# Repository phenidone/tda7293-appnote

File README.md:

# Stereo TDA7293

This is a PCB design for a stereo amplifier, using a TDA7293 for each channel.

## Power

The board requires 36+36V DC for 8R loads.  Filtering caps are included, but 
a bridge rectifier is not as this is expected to be used with a switching supply.

## Unmute

The muting circuits are controlled via an opto-isolated input.  Provide 
5-24VDC on the UNMUTE port to enable the amplifiers.  This port allows the
amplifier to be put into a standby/mute mode, e.g. while preamplifiers are
booting and power supplies are stabilising.

## Components

Input capacitors shall be film-type box capacitors, 5mm lead pitch.

C3 and C9 should be non-polarised 22uF electrolytics, as high-voltage as will
fit in the footprint (8mm with 3.5mm lead pitch).

All resistors in the signal chain (R1, R2, R3, R13, R14, R15) should be thin-film
metal precision resistors.

Loop-break resistors (R7, R8, R17, R18) can be chosen differently in accordance
with different grounding needs, e.g. where multiple modules are powered from a
single PSU but receiving signal from a third preamplifier board.  Their
selection depends on your ground topology.

The output zobels (R5/C6, R16/C12) are probably only necessary with a TDA7294,
and may be omitted if there is absolutely no chance of shorting the amplifier
leads, e.g. through use of insulated plugs instead of bare wires into screw
terminals.  R5 and R16 should be 2W-rated.

## TDA7294

The board charges the bootstrap capacitor from the OUTPUT pin rather than
the BOOTLOAD pin, so this board will also work unmodified with a TDA7294.
That limits the absolute-max supply voltage to 100V rather than 120V, but
the appropriate level is lower than that anyway unless you have a very high
impedance load.

## License

This hardware design is (C) 2021 William Brodie-Tyrrell and is licensed under 
the CERN OHL; see cern_ohl_v_1_2.pdf

## TRL

Rev.A is tested and working, but has not been subjected to EMI or other
regulatory testing.

Rev.B has been manufactured but not tested.

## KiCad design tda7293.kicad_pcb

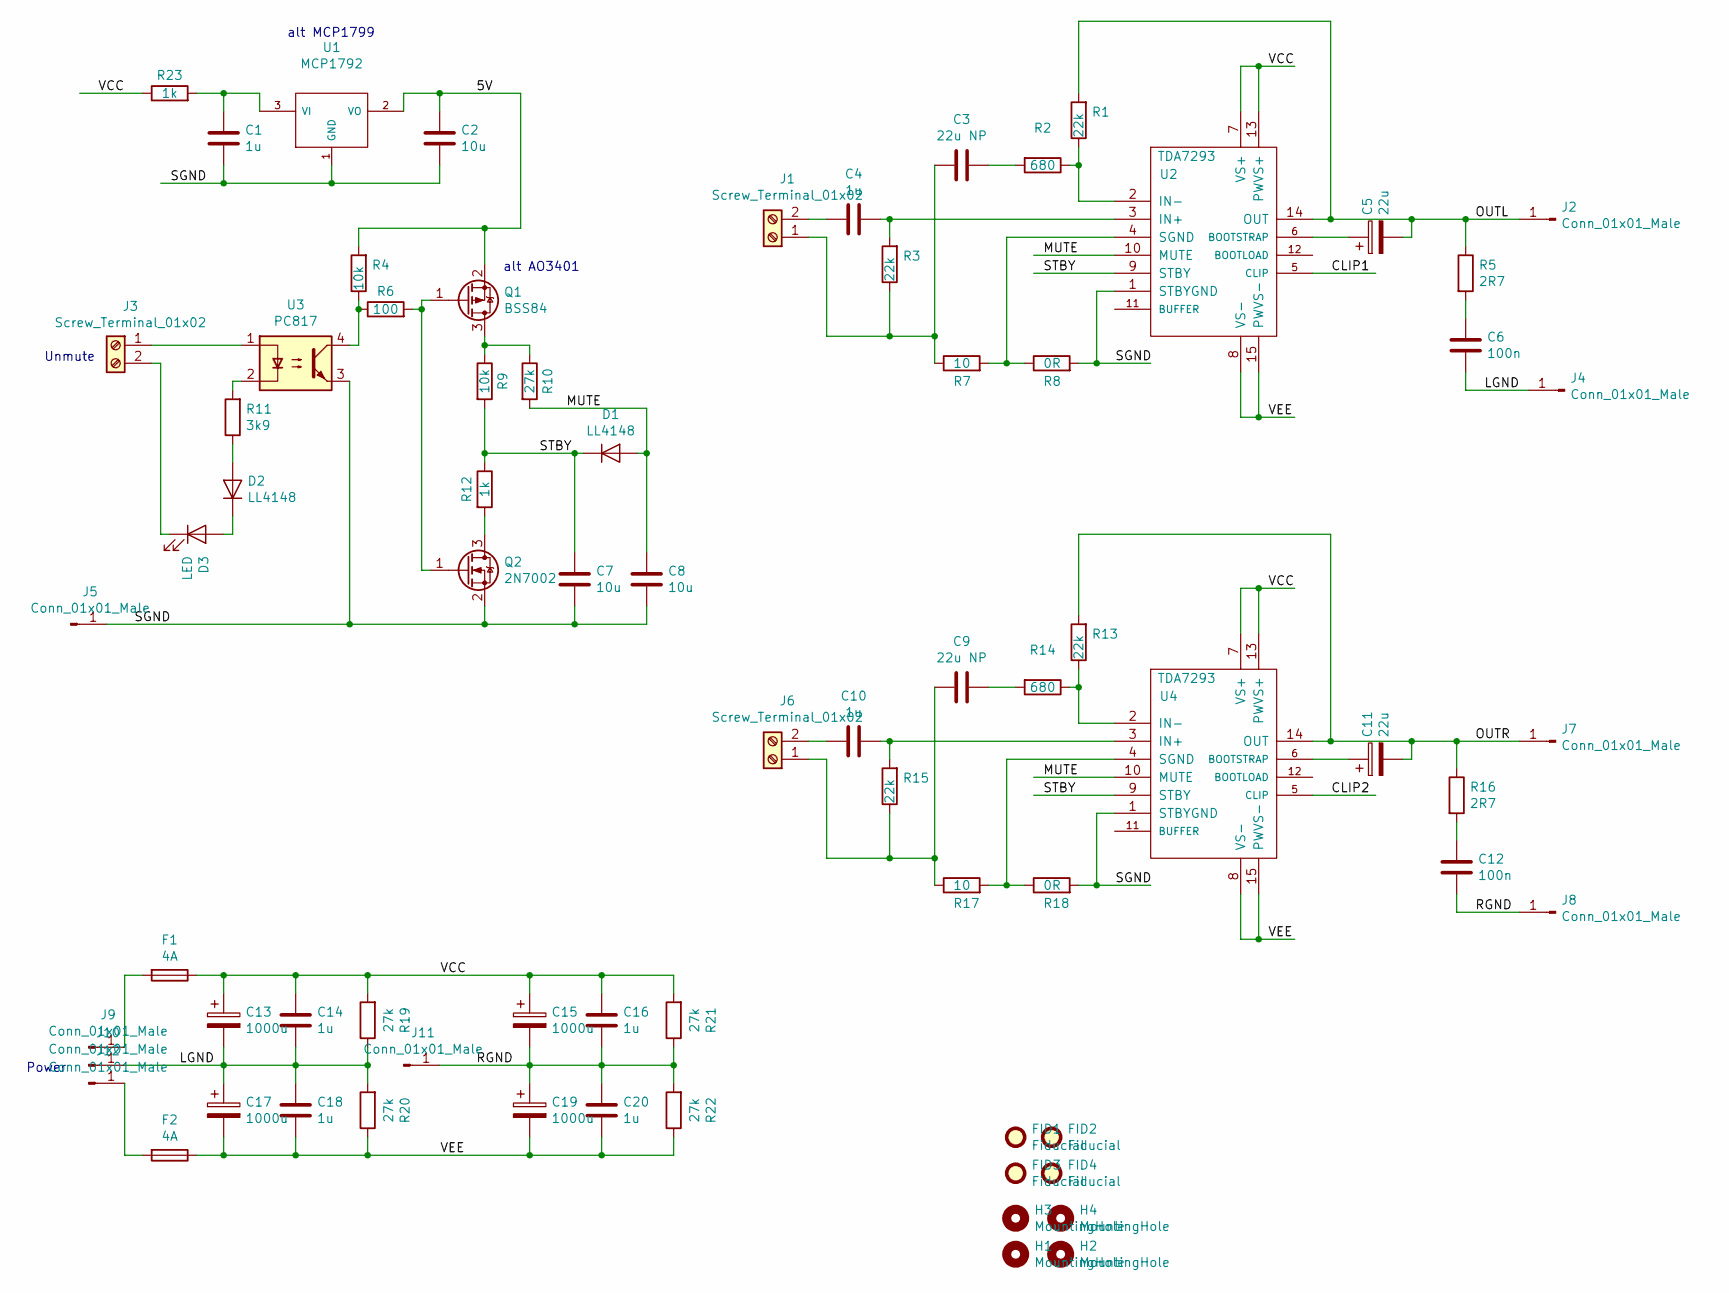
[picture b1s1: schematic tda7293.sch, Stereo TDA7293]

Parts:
C1, C14, C16, C18, C20: 1u; C_0805
C2, C7, C8: 10u; C_0805
C3, C9: 22u NP; CP_Radial_D8.0mm_P3.50mm
C4, C10: 1u; C_Rect_L7.0mm_W3.5mm_P5.00mm
C5, C11: 22u; CP_Radial_D6.3mm_P2.50mm
C6, C12: 100n; C_0805
C13, C15, C17, C19: 1000u; CP_Radial_D16.0mm_P7.50mm
D1, D2: LL4148; D_MiniMELF
D3: LED; LED_0805
F1, F2: 4A; Fuseholder5x20_6mm
FID1, FID2, FID3, FID4: Fiducial; Fiducial_1mm_Dia_2mm_Outer
H1, H2, H3, H4: MountingHole; MountingHole_3.2mm_M3
J1, J3, J6: Screw_Terminal_01x02; TerminalBlock_Phoenix_MPT-2.54mm_2pol
J2, J4, J5, J7, J8, J9, J10, J11, J12: Conn_01x01_Male; FASTON250P_5.08mm_male_vertical
Q1: BSS84; SOT-23
Q2: 2N7002; SOT-23
R1, R3, R13, R15: 22k; R_0805
R2, R14: 680; R_0805
R4, R9: 10k; R_0805
R5, R16: 2R7; R_Axial_DIN0414_L11.9mm_D4.5mm_P5.08mm_Vertical
R6: 100; R_0805
R7, R17: 10; R_0805
R8, R18: 0R; R_0805
R10, R19, R20, R21, R22: 27k; R_0805
R11: 3k9; R_0805
R12, R23: 1k; R_0805
U1: MCP1792; SOT-23
U2, U4: TDA7293; Multiwatt15V
U3: PC817; DIP-4_W7.62mm_Socket

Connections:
/5V: C2.1, Q1.2 (S), R4.2, U1.2 (VO)
/CLIP1: U2.5 (CLIP)
/CLIP2: U4.5 (CLIP)
/LGND: C6.2, C13.2, C14.2, C17.1, C18.1, J4.1, J10.1, R19.1, R20.2
/MUTE: C8.2, D1.2 (A), R10.2, U2.10 (MUTE), U4.10 (MUTE)
/OUTL: C5.2, J2.1, R1.2, R5.1, U2.14 (OUT)
/OUTR: C11.2, J7.1, R13.2, R16.1, U4.14 (OUT)
/RGND: C12.2, C15.2, C16.2, C19.1, C20.1, J8.1, J11.1, R21.1, R22.2
/SGND: C1.2, C2.2, C7.1, C8.1, J5.1, Q2.2 (S), R8.2, R18.2, U1.1 (GND), U2.1 (STBYGND), U3.3, U4.1 (STBYGND)
/STBY: C7.2, D1.1 (K), R9.2, R12.1, U2.9 (STBY), U4.9 (STBY)
/VCC: C13.1, C14.1, C15.1, C16.1, F1.1, R19.2, R21.2, R23.1, U2.7 (VS+), U2.13 (PWVS+), U4.7 (VS+), U4.13 (PWVS+)
/VEE: C17.2, C18.2, C19.2, C20.2, F2.1, R20.1, R22.1, U2.8 (VS-), U2.15 (PWVS-), U4.8 (VS-), U4.15 (PWVS-)
unnamed: C1.1, R23.2, U1.3 (VI)
unnamed: C3.1, R2.2
unnamed: C3.2, J1.1, R3.1, R7.1
unnamed: C4.1, R3.2, U2.3 (IN+)
unnamed: C4.2, J1.2
unnamed: C5.1, U2.6 (BOOTSTRAP)
unnamed: C6.1, R5.2
unnamed: C9.1, R14.2
unnamed: C9.2, J6.1, R15.1, R17.1
unnamed: C10.1, R15.2, U4.3 (IN+)
unnamed: C10.2, J6.2
unnamed: C11.1, U4.6 (BOOTSTRAP)
unnamed: C12.1, R16.2
unnamed: D2.1 (K), D3.2 (A)
unnamed: D2.2 (A), R11.1
unnamed: D3.1 (K), J3.2
unnamed: F1.2, J9.1
unnamed: F2.2, J12.1
unnamed: J3.1, U3.1
unnamed: Q1.1 (G), Q2.1 (G), R6.2
unnamed: Q1.3 (D), R9.1, R10.1
unnamed: Q2.3 (D), R12.2
unnamed: R1.1, R2.1, U2.2 (IN-)
unnamed: R4.1, R6.1, U3.4
unnamed: R7.2, R8.1, U2.4 (SGND)
unnamed: R11.2, U3.2
unnamed: R13.1, R14.1, U4.2 (IN-)
unnamed: R17.2, R18.1, U4.4 (SGND)

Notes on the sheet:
Power
Unmute
alt AO3401
alt MCP1799

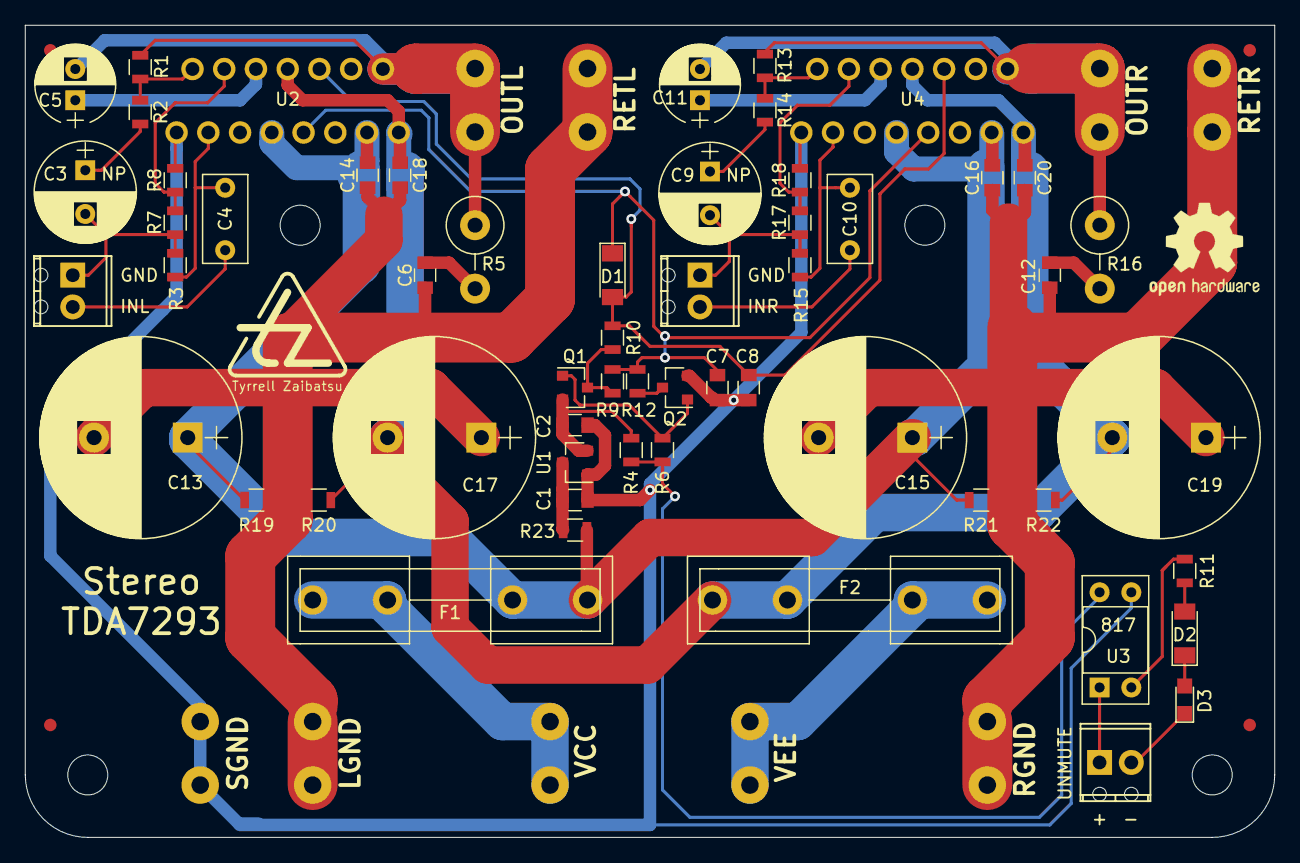
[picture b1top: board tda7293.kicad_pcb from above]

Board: 2 copper layers, 100.0 x 65.0 mm, 74 parts (0 on the bottom side), 38 nets.

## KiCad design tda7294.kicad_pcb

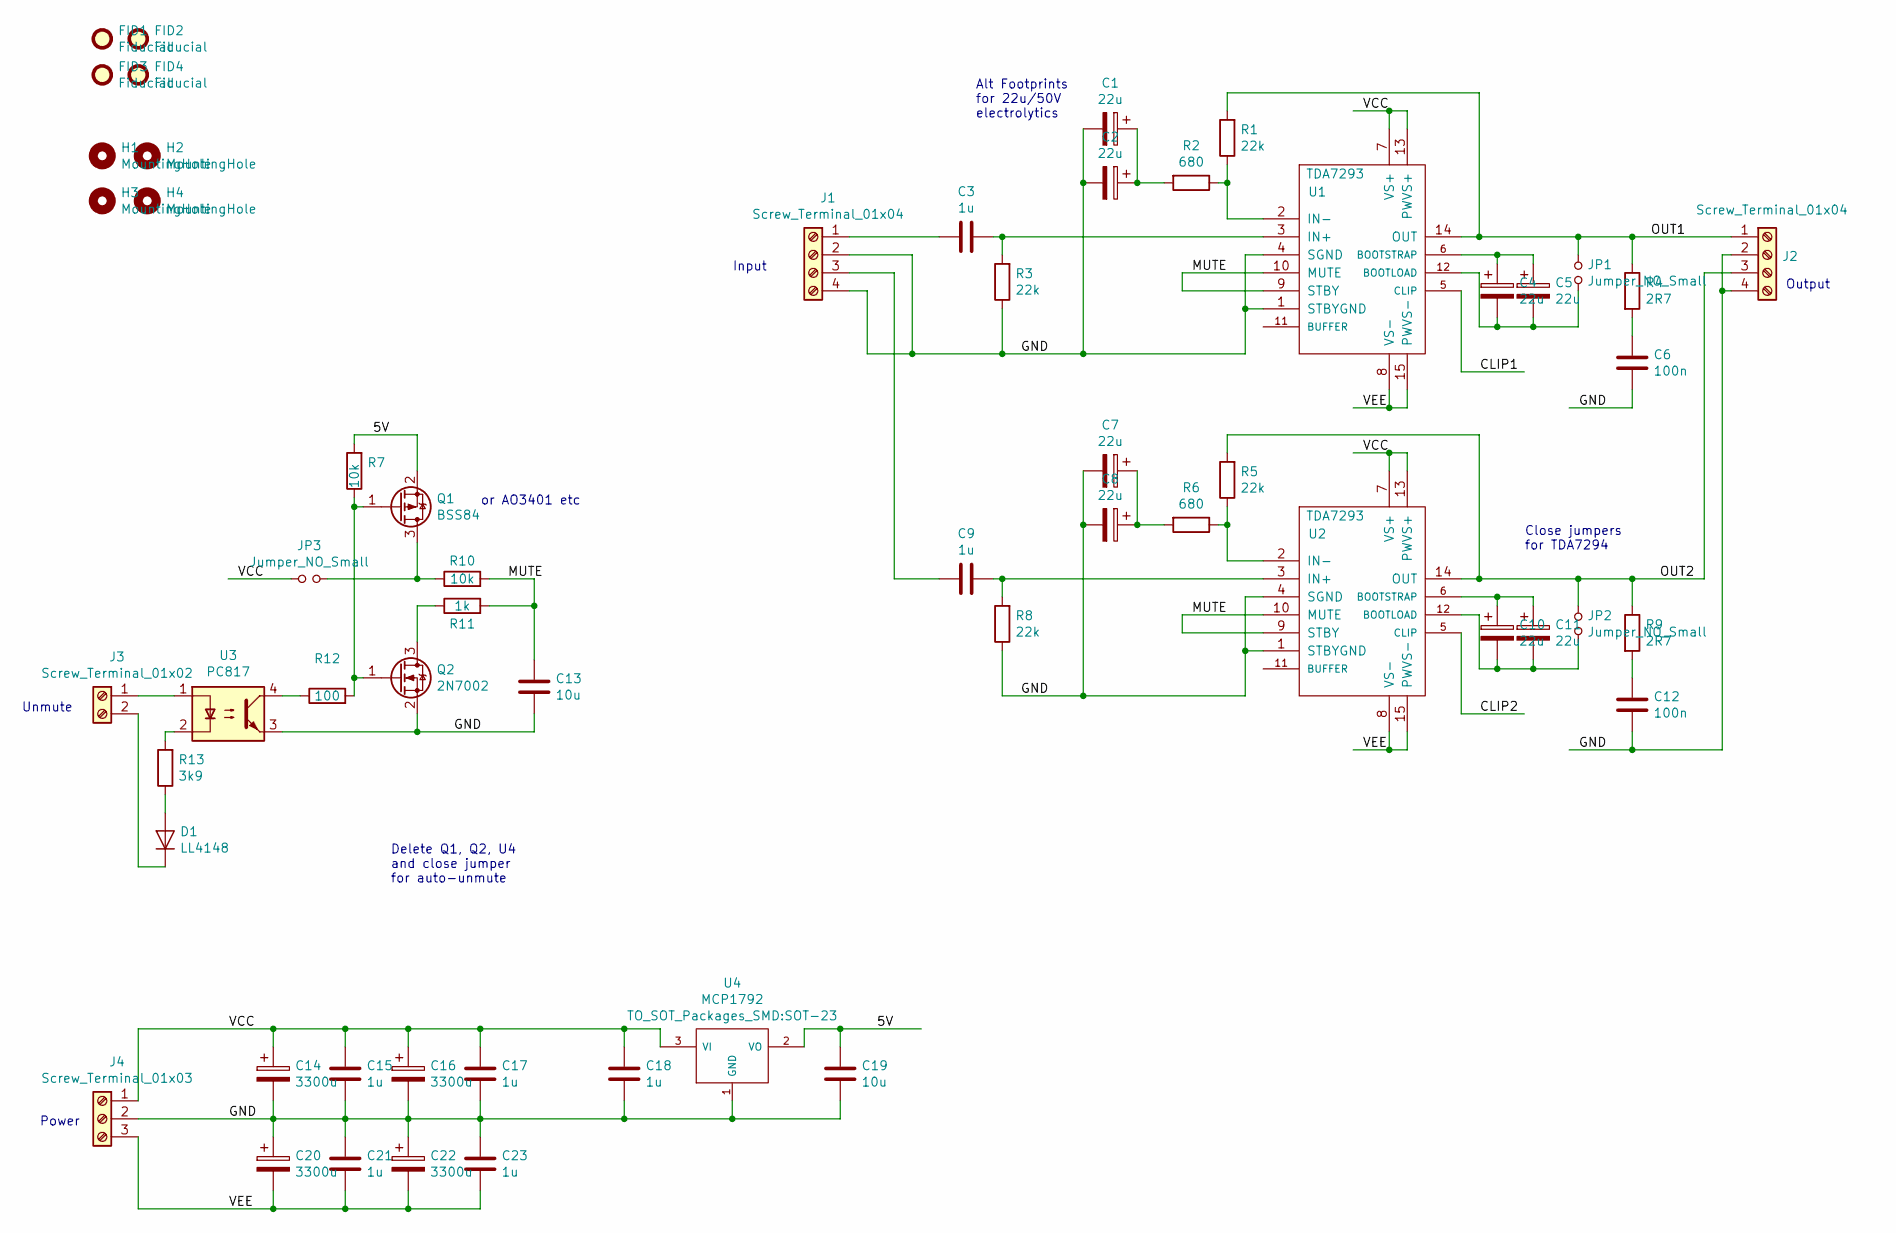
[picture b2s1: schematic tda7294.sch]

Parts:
C1, C4, C7, C10: 22u; CP_Elec_6.3x7.7
C2, C5, C8, C11: 22u; CP_Radial_D5.0mm_P2.00mm
C3, C9: 1u; C_Rect_L7.0mm_W3.5mm_P5.00mm
C6, C12: 100n; C_0805
C13, C19: 10u; C_0805
C14, C16, C20, C22: 3300u; CP_Radial_D18.0mm_P7.50mm
C15, C17, C18, C21, C23: 1u; C_0805
D1: LL4148; D_MiniMELF
FID1, FID2, FID3, FID4: Fiducial; Fiducial_1mm_Dia_2mm_Outer
H1, H2, H3, H4: MountingHole; MountingHole_3.2mm_M3
J1: Screw_Terminal_01x04; TerminalBlock_Phoenix_MPT-2.54mm_4pol
J2: Screw_Terminal_01x04; TerminalBlock_Phoenix_MKDS1.5-4pol
J3: Screw_Terminal_01x02; TerminalBlock_Phoenix_MPT-2.54mm_2pol
J4: Screw_Terminal_01x03; TerminalBlock_Phoenix_MKDS1.5-3pol
JP1, JP2, JP3: Jumper_NO_Small; Pin_Header_Straight_1x02_Pitch2.00mm
Q1: BSS84; SOT-23
Q2: 2N7002; SOT-23
R1, R3, R5, R8: 22k; R_0805
R2, R6: 680; R_0805
R4, R9: 2R7; R_Axial_DIN0414_L11.9mm_D4.5mm_P5.08mm_Vertical
R7, R10: 10k; R_0805
R11: 1k; R_0805
R12: 100; R_0805
R13: 3k9; R_0805
U1, U2: TDA7293; Multiwatt15V
U3: PC817; DIP-4_W7.62mm_Socket
U4: MCP1792; SOT-23

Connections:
/5V: C19.1, Q1.2 (S), R7.2, U4.2 (VO)
/CLIP1: U1.5 (CLIP)
/CLIP2: U2.5 (CLIP)
/GND: C1.2, C2.2, C6.2, C7.2, C8.2, C12.2, C13.1, C14.2, C15.2, C16.2, C17.2, C18.2, C19.2, C20.1, C21.1, C22.1, C23.1, J1.2, J1.4, J2.2, J2.4, J4.2, Q2.2 (S), R3.1, R8.1, U1.1 (STBYGND), U1.4 (SGND), U2.1 (STBYGND), U2.4 (SGND), U3.3, U4.1 (GND)
/MUTE: C13.2, R10.2, R11.2, U1.9 (STBY), U1.10 (MUTE), U2.9 (STBY), U2.10 (MUTE)
/OUT1: J2.1, JP1.1, R1.2, R4.1, U1.14 (OUT)
/OUT2: J2.3, JP2.1, R5.2, R9.1, U2.14 (OUT)
/VCC: C14.1, C15.1, C16.1, C17.1, C18.1, J4.1, JP3.2, U1.7 (VS+), U1.13 (PWVS+), U2.7 (VS+), U2.13 (PWVS+), U4.3 (VI)
/VEE: C20.2, C21.2, C22.2, C23.2, J4.3, U1.8 (VS-), U1.15 (PWVS-), U2.8 (VS-), U2.15 (PWVS-)
unnamed: C1.1, C2.1, R2.2
unnamed: C3.1, R3.2, U1.3 (IN+)
unnamed: C3.2, J1.1
unnamed: C4.1, C5.1, U1.6 (BOOTSTRAP)
unnamed: C4.2, C5.2, JP1.2, U1.12 (BOOTLOAD)
unnamed: C6.1, R4.2
unnamed: C7.1, C8.1, R6.2
unnamed: C9.1, R8.2, U2.3 (IN+)
unnamed: C9.2, J1.3
unnamed: C10.1, C11.1, U2.6 (BOOTSTRAP)
unnamed: C10.2, C11.2, JP2.2, U2.12 (BOOTLOAD)
unnamed: C12.1, R9.2
unnamed: D1.1 (K), J3.2
unnamed: D1.2 (A), R13.1
unnamed: J3.1, U3.1
unnamed: JP3.1, Q1.3 (D), R10.1
unnamed: Q1.1 (G), Q2.1 (G), R7.1, R12.2
unnamed: Q2.3 (D), R11.1
unnamed: R1.1, R2.1, U1.2 (IN-)
unnamed: R5.1, R6.1, U2.2 (IN-)
unnamed: R12.1, U3.4
unnamed: R13.2, U3.2

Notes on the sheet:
Power
Unmute
Output
Input
Alt Footprints for 22u/50V electrolytics
Close jumpers for TDA7294
or AO3401 etc
Delete Q1, Q2, U4 and close jumper for auto-unmute

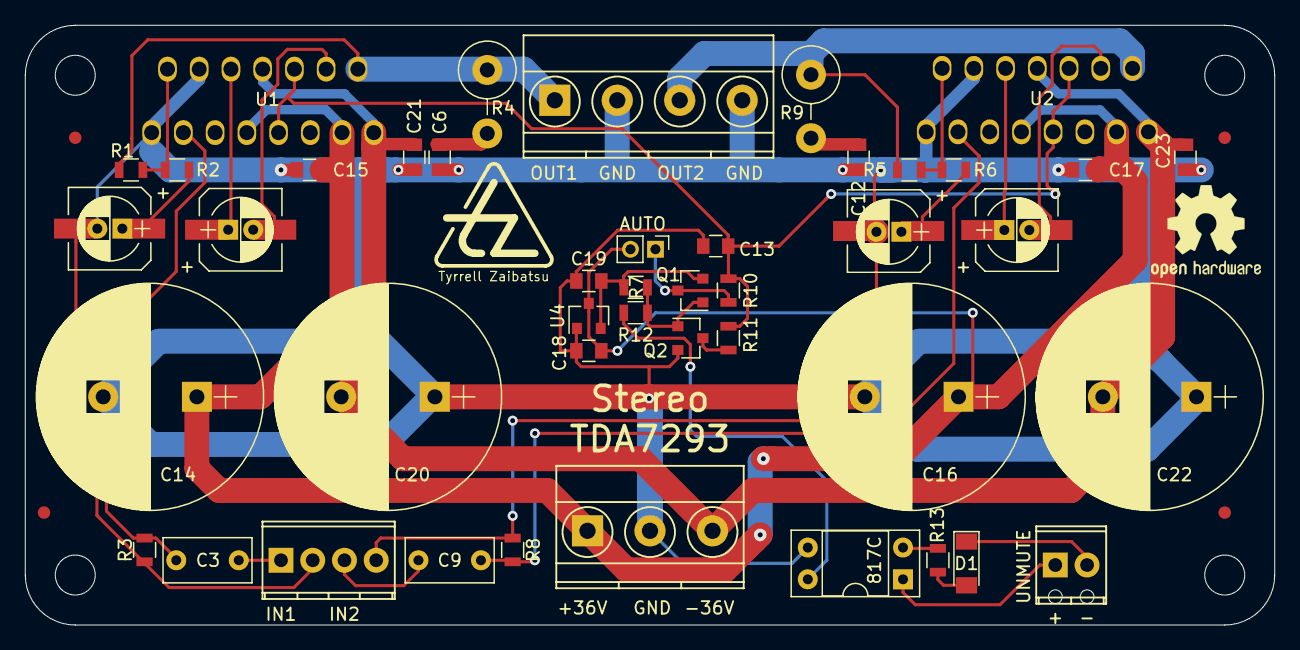
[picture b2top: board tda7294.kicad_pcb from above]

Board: 2 copper layers, 100.0 x 48.0 mm, 56 parts (0 on the bottom side), 29 nets.

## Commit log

2021-11-03 drafted PCB for TDA7293/TDA7294
2021-11-14 Re-routed to separate the signal, power and output grounds
2021-11-14 layout turd-polishing, renamed to TDA7293 due to removal of bootstrap jumper
2021-11-20 C substitutions, status LEDs, layout polishing
2021-11-21 polishing, plotted output, added README
2021-11-24 removed holes, moved input filters, fancier unmute timing per datasheet
2021-11-24 fixed README
2021-11-29 moved a resistor, plotted ready for manufacture
2021-11-29 updated layout PNG
2021-11-29 fixed footprint - matching hole size
2021-11-29 oops
2021-11-30 updated README to show low TRL
2022-01-23 Redrafted as Rev.B: hum-break resistors, better GND topology, fuses, room for heatsink screwdrivers!
2022-04-24 silk-screen updates, turd-polishing, plotted gerbers
2022-04-28 plotted, updated schematic pdf
2022-09-11 updated layout screenshot for Rev.B
